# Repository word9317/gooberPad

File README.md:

# gooberPad
A 9 key macropad that I made for Stardance Hackclub. This is my first time designing a PCB, making a large CAD, and using KMK.

## Features
 - 3x3 Key matrix. All assigned to useful functions
 - Volume knob
 - 0.91" OLED display
 - Silkscreen Timmy(he is cool)
 - KMK firmware
## Keymap
| =D | Column 1 |  Column 2 | Column 3 |
| --- | --- | --- | --- |
| Row 1 | Previous | Pause/Play | Next |
| Row 2 | ALT+TAB | Up arrow | Alt F4 |
| Row 3 | Left arrow | Down arrow | Right arrow |
## Gallery
Case Render

Schematic

PCB

## Firmware
This project uses KMK firmware. Check out [this document](firmware/INFO.md) to learn more.
## BOM
 - 1x Seeed Studio XIAO RP2040
 - 9x DSA Keycaps
 - 9x Cherry MX Switches
 - 4x M3x16 Screws
 - 4x M3 Heat inserts
 - 9x 1N4148 Diodes
 - 1x EC11 Rotary Encoder
 - 1x 128x32 0.91" OLED
 - 1x PCB
 - 1x 3D printed case

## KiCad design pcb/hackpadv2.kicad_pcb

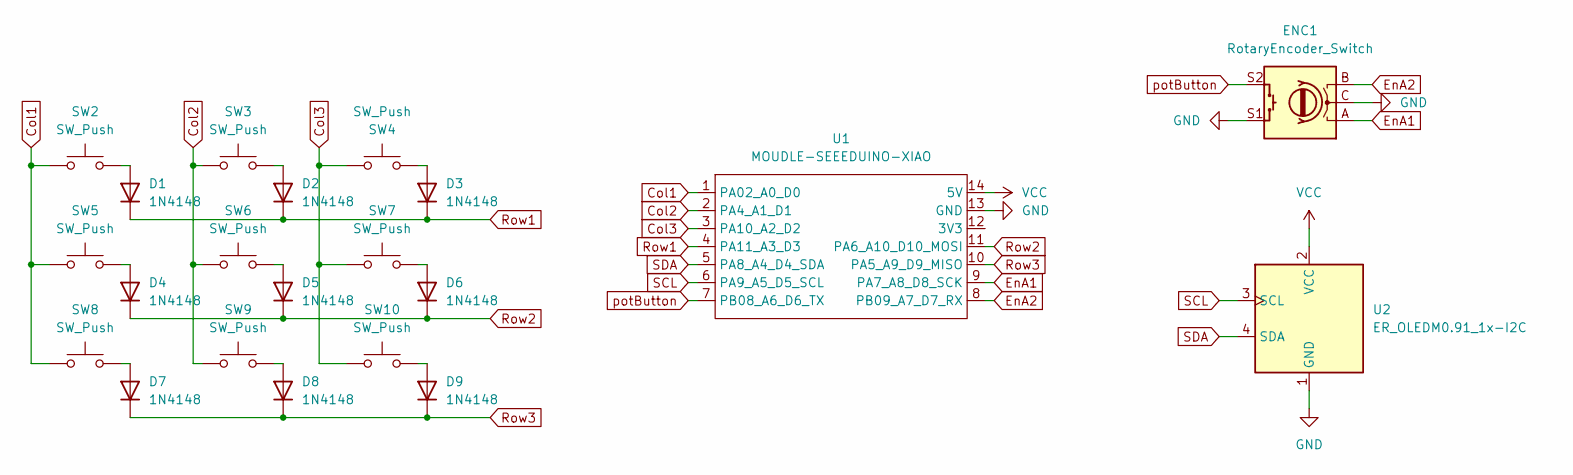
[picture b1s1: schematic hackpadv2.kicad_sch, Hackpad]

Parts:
D1, D2, D3, D4, D5, D6, D7, D8, D9: 1N4148; D_DO-35_SOD27_P7.62mm_Horizontal
ENC1: RotaryEncoder_Switch; RotaryEncoder_Alps_EC11E-Switch_Vertical_H20mm
SW2, SW3, SW4, SW5, SW6, SW7, SW8, SW9, SW10: SW_Push; SW_Cherry_MX_1.00u_PCB
U1: MOUDLE-SEEEDUINO-XIAO; XIAO-Generic-Hybrid-14P-2.54-21X17.8MM
U2: ER_OLEDM0.91_1x-I2C

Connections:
Col1: SW2.1, SW5.1, SW8.1, U1.1 (PA02_A0_D0)
Col2: SW3.1, SW6.1, SW9.1, U1.2 (PA4_A1_D1)
Col3: SW4.1, SW7.1, SW10.1, U1.3 (PA10_A2_D2)
EnA1: ENC1.A, U1.9 (PA7_A8_D8_SCK)
EnA2: ENC1.B, U1.8 (PB09_A7_D7_RX)
GND: ENC1.C, ENC1.S1, U1.13 (GND), U2.1 (GND)
unnamed: D1.2 (A), SW2.2
unnamed: D2.2 (A), SW3.2
unnamed: D3.2 (A), SW4.2
unnamed: D4.2 (A), SW5.2
unnamed: D5.2 (A), SW6.2
unnamed: D6.2 (A), SW7.2
unnamed: D7.2 (A), SW8.2
unnamed: D8.2 (A), SW9.2
unnamed: D9.2 (A), SW10.2
Row1: D1.1 (K), D2.1 (K), D3.1 (K), U1.4 (PA11_A3_D3)
Row2: D4.1 (K), D5.1 (K), D6.1 (K), U1.11 (PA6_A10_D10_MOSI)
Row3: D7.1 (K), D8.1 (K), D9.1 (K), U1.10 (PA5_A9_D9_MISO)
SCL: U1.6 (PA9_A5_D5_SCL), U2.3 (SCL)
SDA: U1.5 (PA8_A4_D4_SDA), U2.4 (SDA)
VCC: U1.14 (5V), U2.2 (VCC)
potButton: ENC1.S2, U1.7 (PB08_A6_D6_TX)

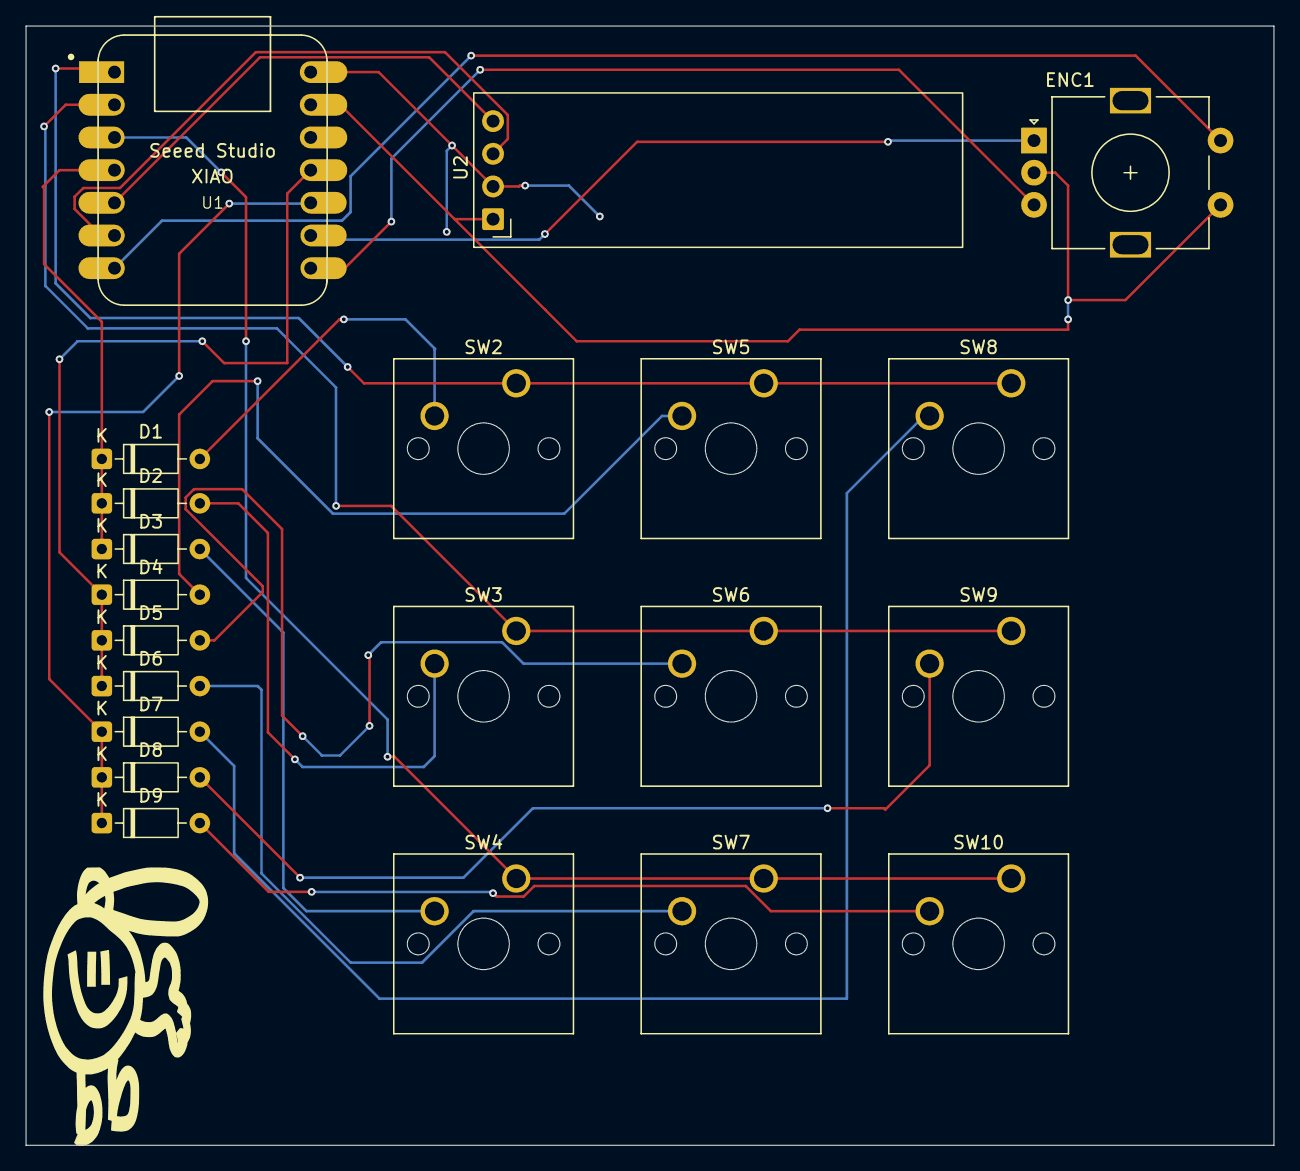
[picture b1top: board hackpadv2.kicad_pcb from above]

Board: 2 copper layers, 97.0 x 87.0 mm, 21 parts (0 on the bottom side), 22 nets.
